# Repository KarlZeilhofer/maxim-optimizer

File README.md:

# Maxim Optimizer

This KiCad project implements a solar cell optimizer based on the Maxim MAX20801 step down controller with integreated MPPT. 

It's inputs are connected to 3 arrays of 20 to 24 solar cells, they have to be isolated on the input side of the optimizer. 

The outputs of the 3 step down controllers are connected in series. 

This kind of optimizer maximizes the output power for each cell array individually, and works perfectly if some solar modules are shaded partially in a string of many modules.

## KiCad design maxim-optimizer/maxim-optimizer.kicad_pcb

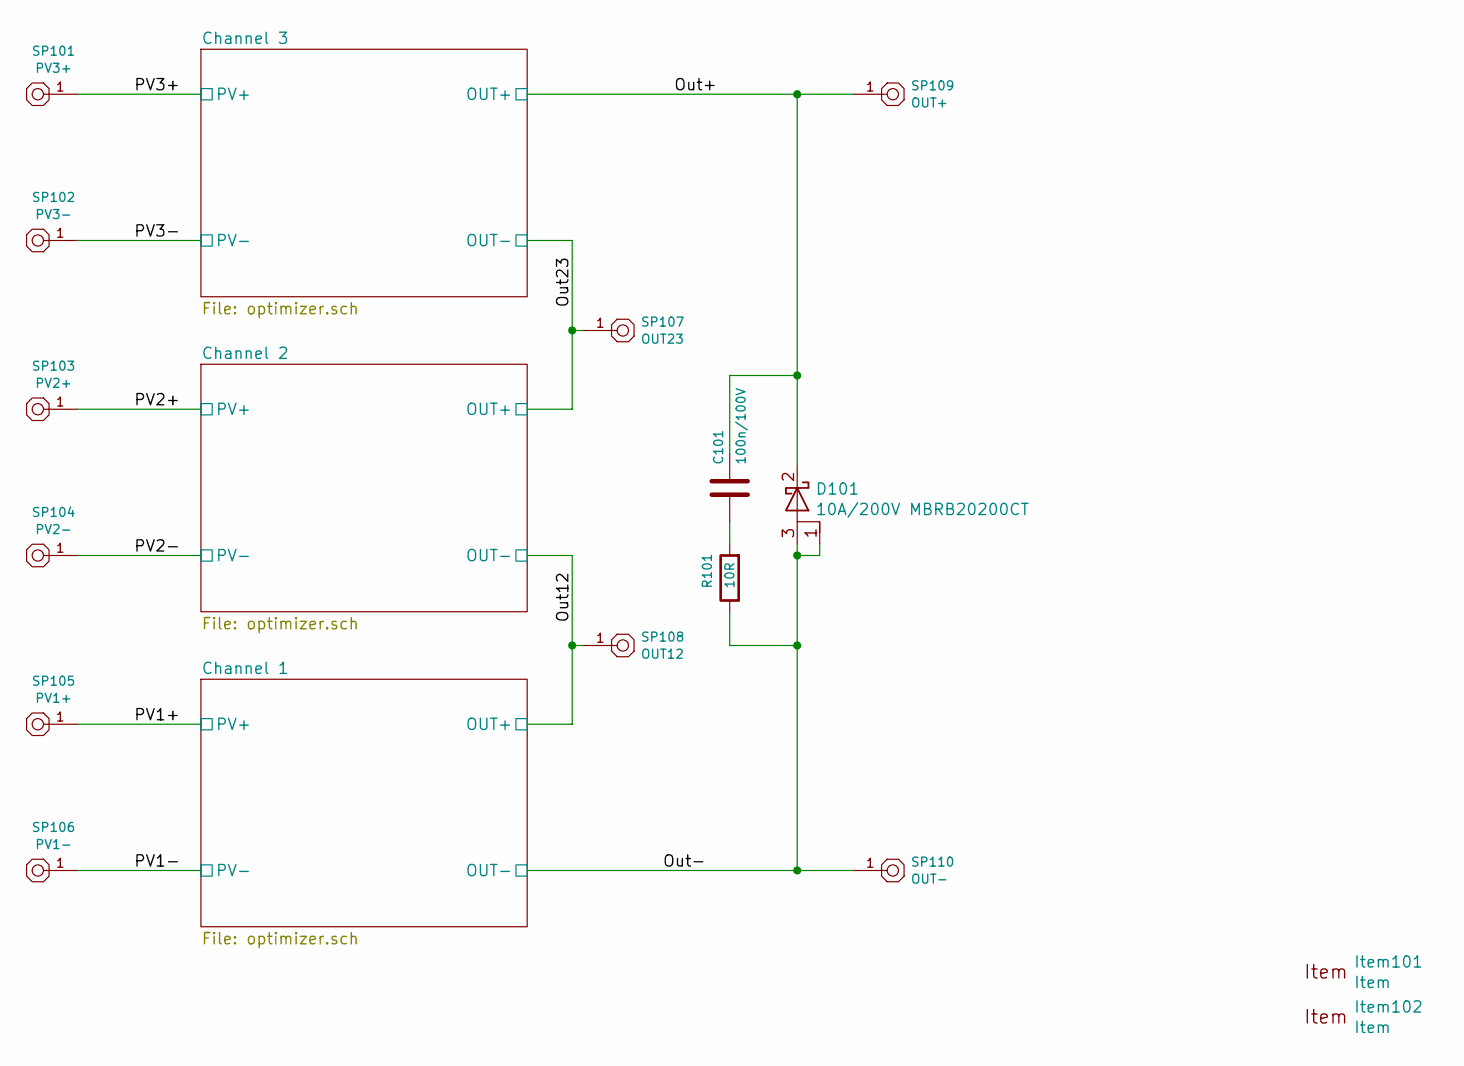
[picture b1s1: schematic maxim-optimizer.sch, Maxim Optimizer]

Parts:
C101: 100n/100V; C1608m
D101: 10A/200V MBRB20200CT; DPAK-2
Item101: Item; team14-logo-icon-0.47
Item102: Item; team14-logo-schrift-0.47
R101: 10R; R1608m
SP101: PV3+; TestPoint_THTPad_D4.0mm_Drill2.0mm
SP102: PV3-; TestPoint_THTPad_D4.0mm_Drill2.0mm
SP103: PV2+; TestPoint_THTPad_D4.0mm_Drill2.0mm
SP104: PV2-; TestPoint_THTPad_D4.0mm_Drill2.0mm
SP105: PV1+; TestPoint_THTPad_D4.0mm_Drill2.0mm
SP106: PV1-; TestPoint_THTPad_D4.0mm_Drill2.0mm
SP107: OUT23; TestPoint_THTPad_D4.0mm_Drill2.0mm
SP108: OUT12; TestPoint_THTPad_D4.0mm_Drill2.0mm
SP109: OUT+; TestPoint_THTPad_D4.0mm_Drill2.0mm
SP110: OUT-; TestPoint_THTPad_D4.0mm_Drill2.0mm

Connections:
/Out12: SP104.1, SP108.1; also elsewhere on the board
/Out23: SP102.1, SP107.1; also elsewhere on the board
/Out+: C101.1, D101.2 (K), SP109.1; also elsewhere on the board
/Out-: D101.1 (A), D101.3 (A), R101.2, SP106.1, SP110.1; also elsewhere on the board
/PV1+: SP105.1; also elsewhere on the board
/PV2+: SP103.1; also elsewhere on the board
/PV3+: SP101.1; also elsewhere on the board
unnamed: C101.2, R101.1

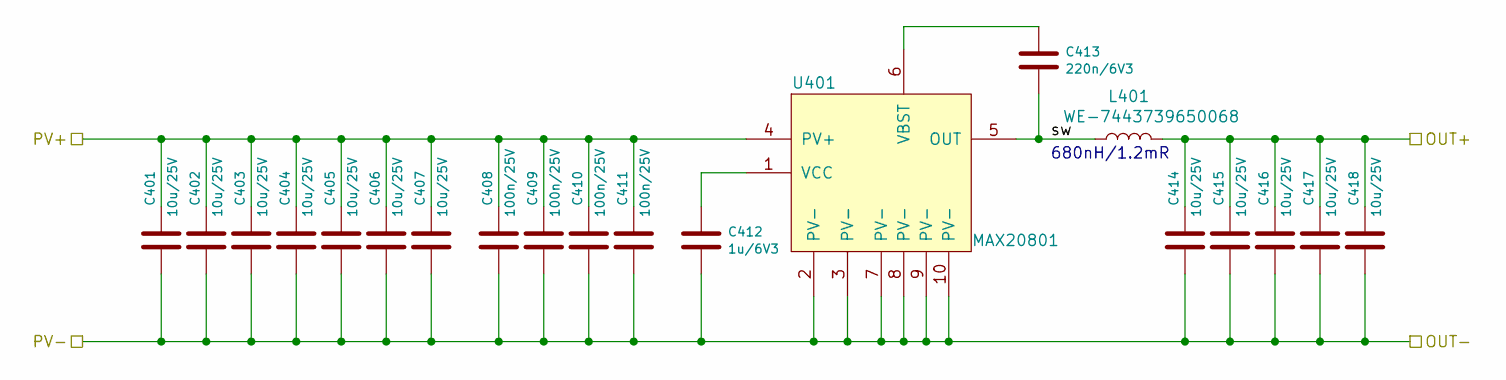
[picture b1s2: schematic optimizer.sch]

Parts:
C201, C202, C203, C204, C205, C206, C207, C214, C215, C216, C217, C218: 10u/25V; C2012m
C208, C209, C210, C211: 100n/25V; C1608m
C212: 1u/6V3; C1608m
C213: 220n/6V3; C1608m
L201: WE-7443739650068; WE-LHMI_1365
U201: MAX20801

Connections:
/Channel 1/sw: C213.2, L201.1, U201.5 (OUT)
/Out12: C214.1, C215.1, C216.1, C217.1, C218.1, L201.2; also elsewhere on the board
/Out-: C201.2, C202.2, C203.2, C204.2, C205.2, C206.2, C207.2, C208.2, C209.2, C210.2, C211.2, C212.2, C214.2, C215.2, C216.2, C217.2, C218.2, U201.2 (PV-), U201.3 (PV-), U201.7 (PV-), U201.8 (PV-), U201.9 (PV-), U201.10 (PV-); also elsewhere on the board
/PV1+: C201.1, C202.1, C203.1, C204.1, C205.1, C206.1, C207.1, C208.1, C209.1, C210.1, C211.1, U201.4 (PV+); also elsewhere on the board
unnamed: C212.1, U201.1 (VCC)
unnamed: C213.1, U201.6 (VBST)

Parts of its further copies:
C301, C302, C303, C304, C305, C306, C307, C314, C315, C316, C317, C318, C401, C402, C403, C404, C405, C406, C407, C414, C415, C416, C417, C418: 10u/25V; C2012m
C308, C309, C310, C311, C408, C409, C410, C411: 100n/25V; C1608m
C312, C412: 1u/6V3; C1608m
C313, C413: 220n/6V3; C1608m
L301, L401: WE-7443739650068; WE-LHMI_1365
U301, U401: MAX20801

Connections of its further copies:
/Channel 2/sw: C313.2, L301.1, U301.5 (OUT)
/Channel 3/sw: C413.2, L401.1, U401.5 (OUT)
/Out12: C301.2, C302.2, C303.2, C304.2, C305.2, C306.2, C307.2, C308.2, C309.2, C310.2, C311.2, C312.2, C314.2, C315.2, C316.2, C317.2, C318.2, U301.2 (PV-), U301.3 (PV-), U301.7 (PV-), U301.8 (PV-), U301.9 (PV-), U301.10 (PV-); also elsewhere on the board
/Out23: C314.1, C315.1, C316.1, C317.1, C318.1, C401.2, C402.2, C403.2, C404.2, C405.2, C406.2, C407.2, C408.2, C409.2, C410.2, C411.2, C412.2, C414.2, C415.2, C416.2, C417.2, C418.2, L301.2, U401.2 (PV-), U401.3 (PV-), U401.7 (PV-), U401.8 (PV-), U401.9 (PV-), U401.10 (PV-); also elsewhere on the board
/Out+: C414.1, C415.1, C416.1, C417.1, C418.1, L401.2; also elsewhere on the board
/PV2+: C301.1, C302.1, C303.1, C304.1, C305.1, C306.1, C307.1, C308.1, C309.1, C310.1, C311.1, U301.4 (PV+); also elsewhere on the board
/PV3+: C401.1, C402.1, C403.1, C404.1, C405.1, C406.1, C407.1, C408.1, C409.1, C410.1, C411.1, U401.4 (PV+); also elsewhere on the board
unnamed: C312.1, U301.1 (VCC)
unnamed: C313.1, U301.6 (VBST)
unnamed: C412.1, U401.1 (VCC)
unnamed: C413.1, U401.6 (VBST)

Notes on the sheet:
680nH/1.2mR

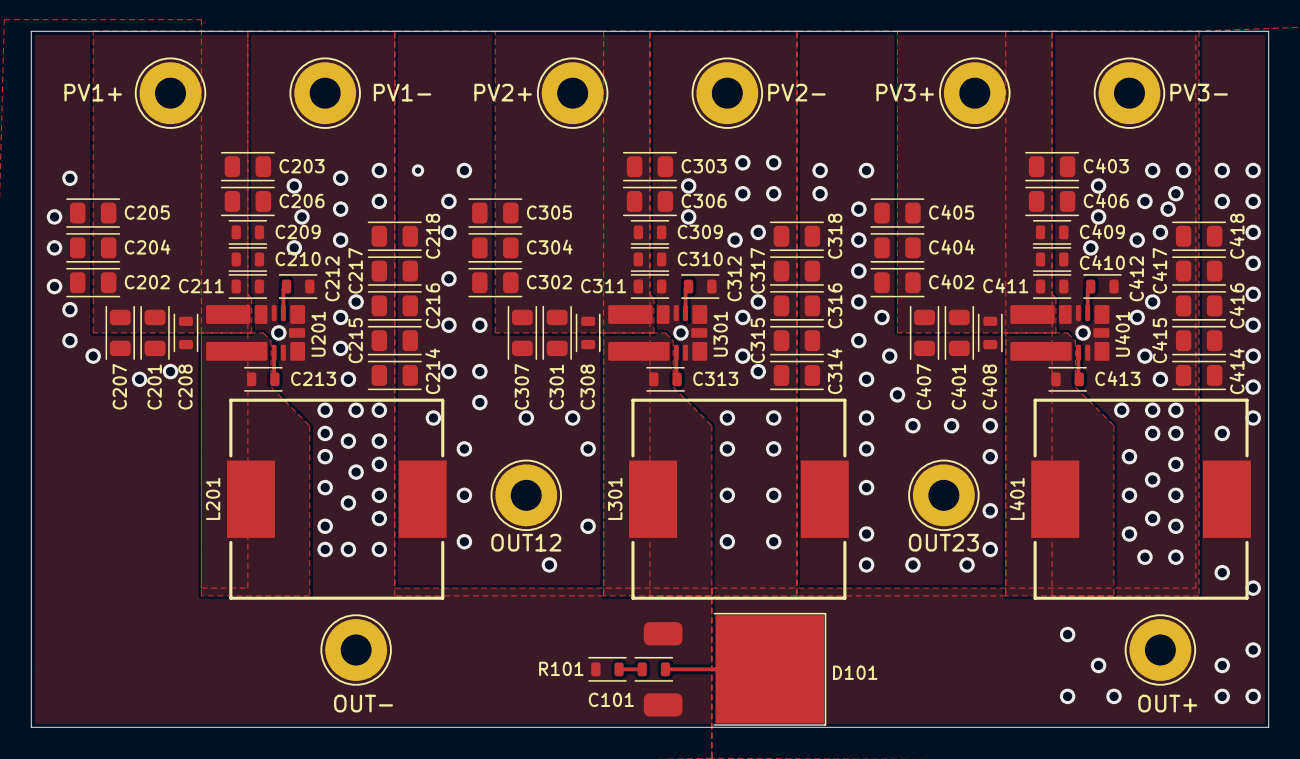
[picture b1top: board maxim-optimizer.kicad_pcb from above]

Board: 2 copper layers, 80.0 x 45.0 mm, 75 parts (0 on the bottom side), 17 nets.

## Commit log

2020-09-19 v20.0.0 preliminary
2020-09-19 readme
2020-09-19 fix typo
2020-09-19 as ordered
2020-09-19 add VI-Limits
2020-09-19 add VI-Limits fix typo
2020-09-20 updated cost calculation
